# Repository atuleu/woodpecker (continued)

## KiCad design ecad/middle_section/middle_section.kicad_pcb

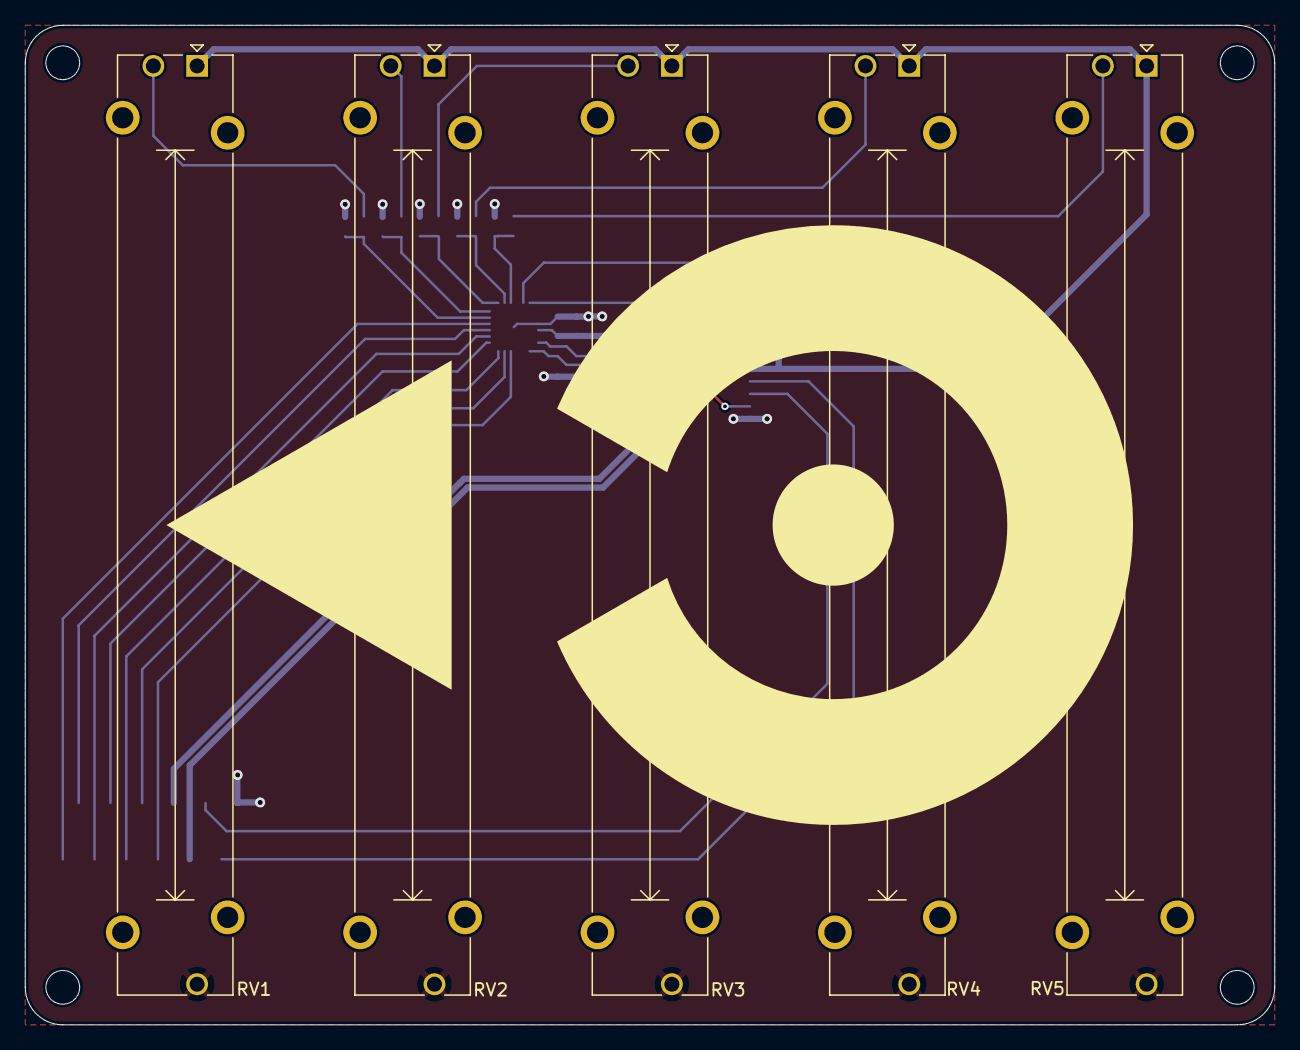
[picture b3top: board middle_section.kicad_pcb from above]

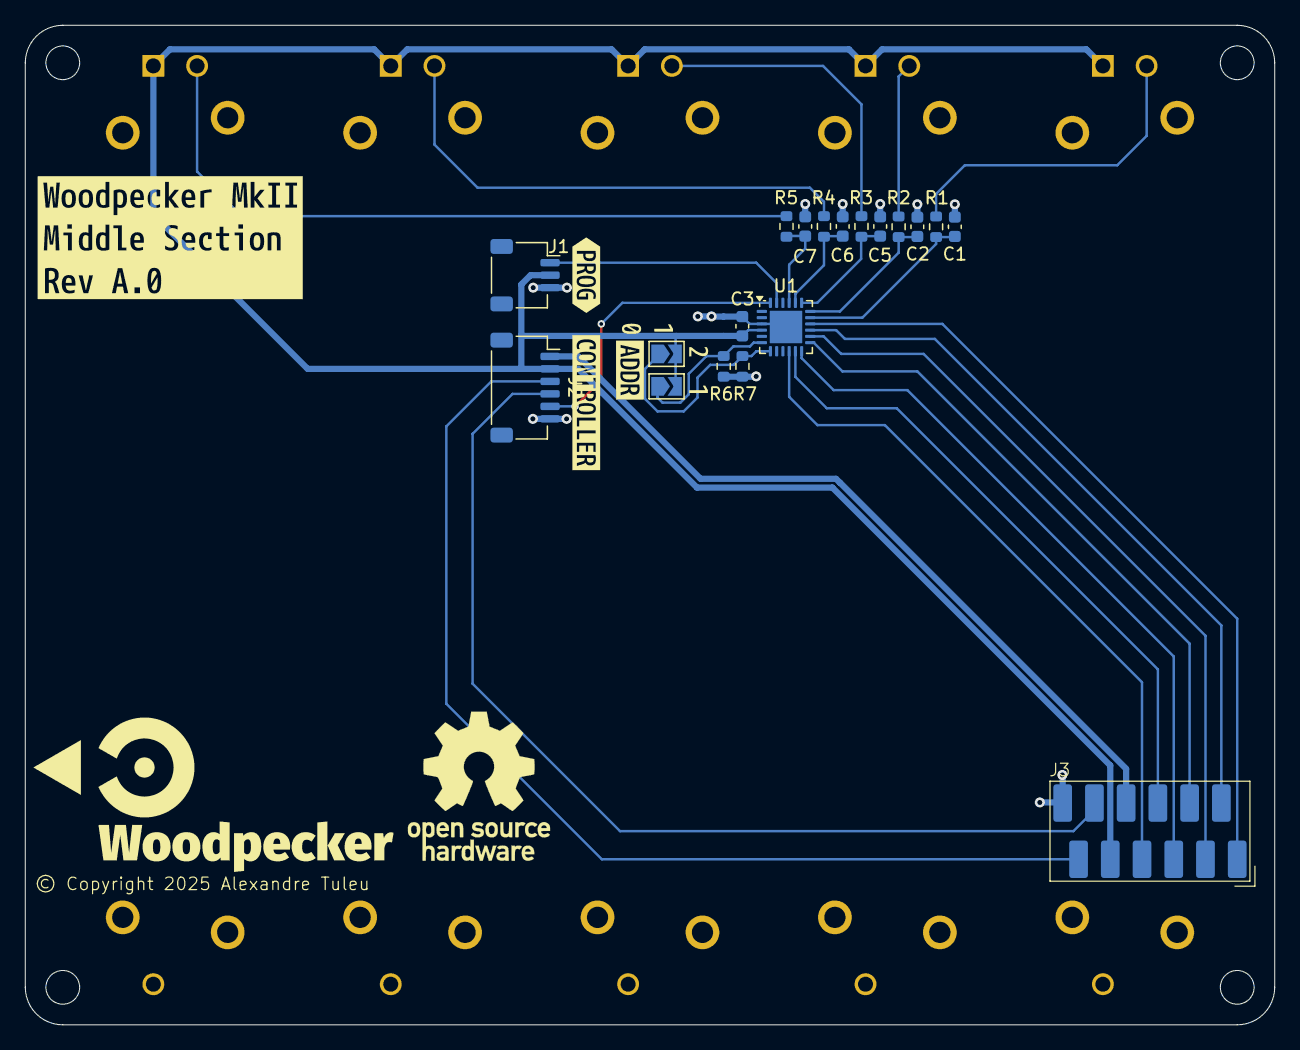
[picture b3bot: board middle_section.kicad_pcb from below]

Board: 2 copper layers, 100.0 x 80.0 mm, 30 parts (25 on the bottom side), 26 nets.

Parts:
C1, C2, C5, C6, C7: 10n; C_0603_1608Metric
C3: 100n; C_0603_1608Metric
J1: JST SH; JST_SH_SM03B-SRSS-TB_1x03-1MP_P1.00mm_Horizontal
J2: JST SH 6P; JST_SH_SM06B-SRSS-TB_1x06-1MP_P1.00mm_Horizontal
J3: Micro-MaTch 2x06; TE_Micro-MaTch_1-188275-2_2x06_P1.27mm_Vertical
JP1, JP2: SolderJumper_2_Open; SolderJumper-2_P1.3mm_Open_TrianglePad1.0x1.5mm
R1, R2, R3, R4, R5: 100; R_0603_1608Metric
R6, R7: 33k; R_0603_1608Metric
RV1, RV2, RV3, RV4, RV5: PTA6043; Potentiometer_Bourns_PTA6043_Single_Slide
U1: ATtiny1617-M; QFN-24-1EP_4x4mm_P0.5mm_EP2.6x2.6mm
kibuzzard-68CC21B9: G***; kibuzzard-68CC21B9
kibuzzard-68CC21E1: G***; kibuzzard-68CC21E1
kibuzzard-68CC21F8: G***; kibuzzard-68CC21F8
kibuzzard-68CC26E5: G***; kibuzzard-68CC26E5
kibuzzard-68CC214D: G***; kibuzzard-68CC214D
kibuzzard-68CC259B: G***; kibuzzard-68CC259B

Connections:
+3V3: C3.1, J1.2, J2.2, J3.9, JP1.2 (B), JP2.2 (B), RV1.1, RV2.1, RV3.1, RV4.1, RV5.1, U1.4 (VCC)
+5V: J2.1, J3.8
/A0: JP1.1 (A), R6.1, U1.6 (PA5)
/A1: JP2.1 (A), R7.1, U1.7 (PA6)
/CH0: C1.1, R1.2, U1.17 (PC0)
/CH0_RAW: R1.1, RV1.2
/CH1: C2.1, R2.2, U1.18 (PC1)
/CH1_RAW: R2.1, RV2.2
/CH2: C5.1, R3.2, U1.19 (PC2)
/CH2_RAW: R3.1, RV3.2
/CH3: C6.1, R4.2, U1.20 (PC3)
/CH3_RAW: R4.1, RV4.2
/CH4: C7.1, R5.2, U1.21 (PC4)
/CH4_RAW: R5.1, RV5.2
/COL1: J3.1, U1.16 (PB0)
/COL2: J3.2, U1.15 (PB1)
/COL3: J3.3, U1.14 (PB2)
/COL4: J3.4, U1.13 (PB3)
/COL5: J3.5, U1.12 (PB4)
/R5_SW: J3.7, U1.10 (PB6)
/R6_SW: J3.6, U1.11 (PB5)
/SCL: J2.4, J3.10
/SDA: J2.3, J3.11
/TX: J2.5, U1.24 (PA1)
/UDPI: J1.1, U1.23 (~RESET/PA0)
GND: C1.2, C2.2, C3.2, C5.2, C6.2, C7.2, J1.3, J2.6, J3.12, R6.2, R7.2, RV1.3, RV2.3, RV3.3, RV4.3, RV5.3, U1.3 (GND), U1.25 (GND)

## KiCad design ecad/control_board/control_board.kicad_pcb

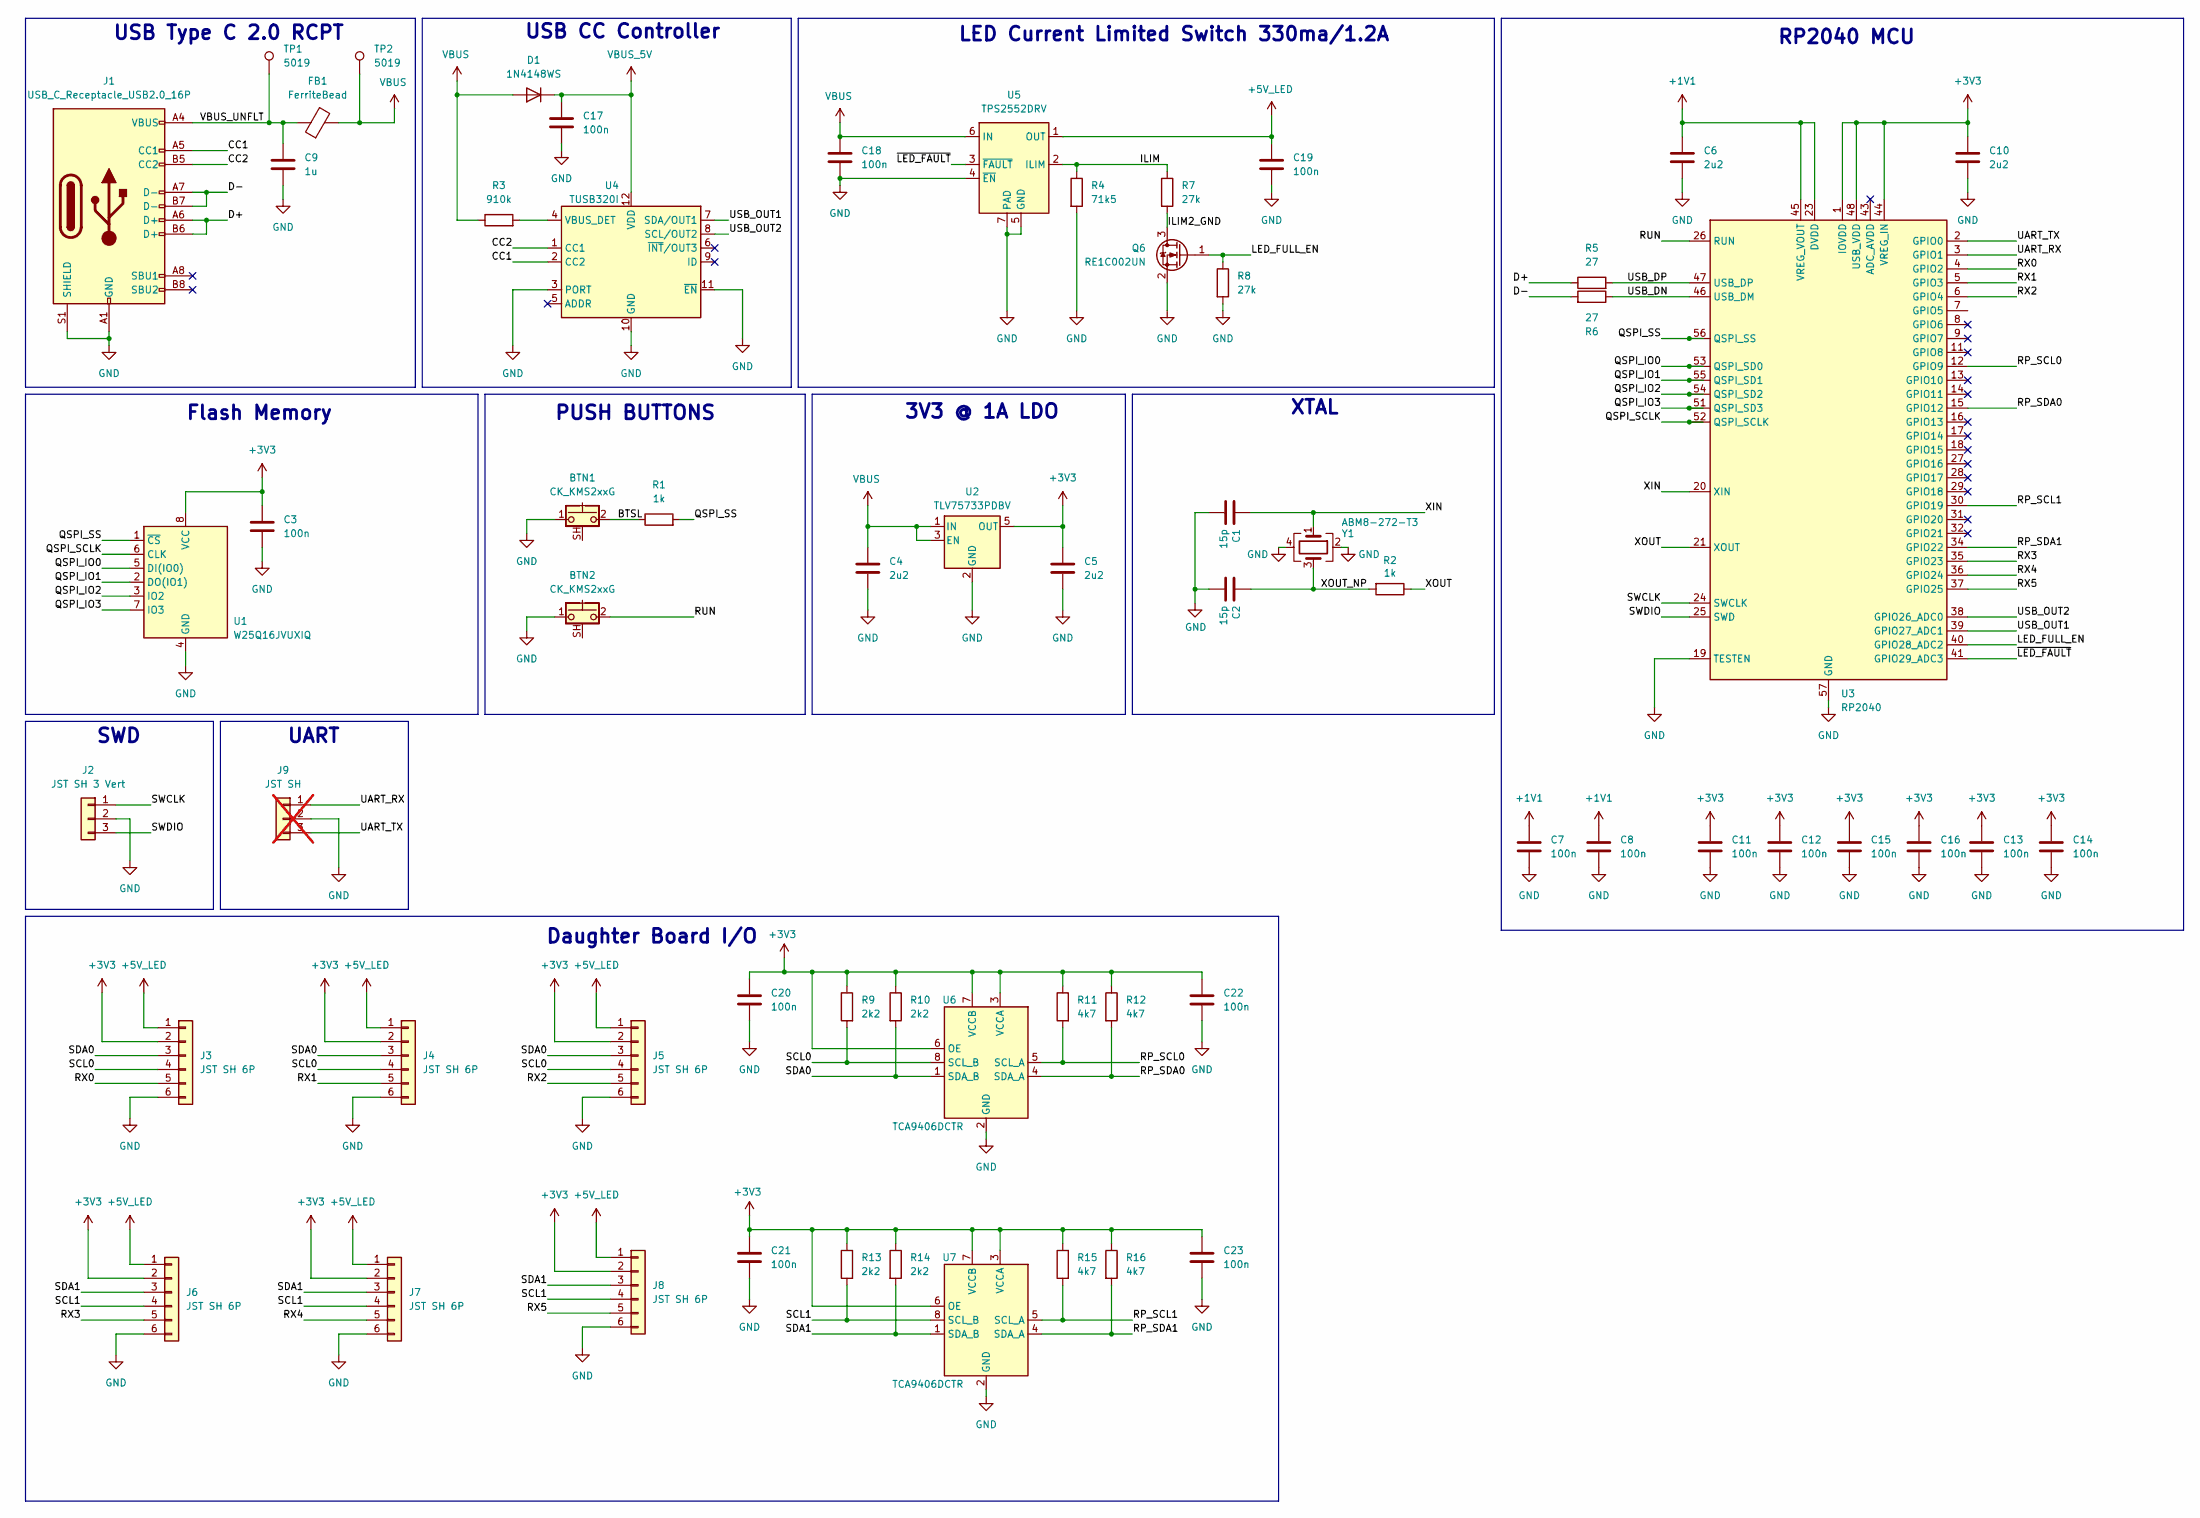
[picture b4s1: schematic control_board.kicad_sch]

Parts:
BTN1, BTN2: CK_KMS2xxG; SW_SPST_CK_KMS2xxGP; MPN KMS231GP LFS
C1, C2: 15p; C_0402_1005Metric; MPN GCM1555C1H150JA16D
C3, C7, C8, C11, C12, C13, C14, C15, C16, C17, C18, C19: 100n; C_0402_1005Metric; MPN CL05B104KP5NNNC
C4, C5: 2u2; C_0603_1608Metric; MPN CL10B225KP8NNNC
C6, C10: 2u2; C_0402_1005Metric; MPN GRM155Z71A225KE01D
C9: 1u; C_0603_1608Metric; MPN CL10B105KP8NNNC
C20, C21, C22, C23: 100n; C_0603_1608Metric; MPN CL10B104KB8NNWC
D1: 1N4148WS; D_SOD-323; MPN 1N4148WS
FB1: FerriteBead; R_1206_3216Metric; MPN HCB 3216KF-501T30
J1: USB_C_Receptacle_USB2.0_16P; USB_C_Receptacle_GCT_USB4105-xx-A_16P_TopMnt_Horizontal; MPN USB4105-GF-A
J2: JST SH 3 Vert; JST_SH_SM03B-SRSS-TB_1x03-1MP_P1.00mm_Horizontal; MPN SM03B-SRSS-TB
J3, J4, J5, J6, J7, J8: JST SH 6P; JST_SH_SM06B-SRSS-TB_1x06-1MP_P1.00mm_Horizontal; MPN SM06B-SRSS-TB
J9: JST SH; JST_SH_SM03B-SRSS-TB_1x03-1MP_P1.00mm_Horizontal; MPN BM03B-SRSS-TB; not fitted
Q6: RE1C002UN; SOT-416; MPN RE1C002UN
R1, R2: 1k; R_0402_1005Metric; MPN RC0402FR-071KL
R3: 910k; R_0402_1005Metric; MPN RC0402FR-07910KL
R4: 71k5; R_0402_1005Metric; MPN RC0402FR-1371K5L
R5, R6: 27; R_0402_1005Metric; MPN RC0402FR-0727RL
R7, R8: 27k; R_0402_1005Metric; MPN RC0402FR-0727KL
R9, R10, R13, R14: 2k2; R_0603_1608Metric; MPN RC0603FR-072K2L
R11, R12, R15, R16: 4k7; R_0603_1608Metric; MPN RC0603FR-074K7L
TP1, TP2: 5019; TestPoint_Keystone_5019_Miniature; MPN 5019
U1: W25Q16JVUXIQ; Winbond_USON-8-1EP_3x2mm_P0.5mm_EP0.2x1.6mm; MPN W25Q16JVUXIQ TR
U2: TLV75733PDBV; SOT-23-5; MPN TLV75733PDBV
U3: RP2040; QFN-56-1EP_7x7mm_P0.4mm_EP3.2x3.2mm; MPN RP2040
U4: TUSB320I; Texas_X2QFN-12_1.6x1.6mm_P0.4mm; MPN TUSB320LI
U5: TPS2552DRV; Texas_WSON-6-1EP_2x2mm_P0.65mm_EP1x1.6mm_ThermalVias; MPN TPS2552DRVR
U6, U7: TCA9406DCTR; SSOP-8_2.95x2.8mm_P0.65mm; MPN TCA9406DCTR
Y1: ABM8-272-T3; Crystal_SMD_3225-4Pin_3.2x2.5mm; MPN ABM8-272-T3

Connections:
+1V1: C6.1, C7.1, C8.1, U3.23 (DVDD), U3.45 (VREG_VOUT), U3.50 (DVDD)
+3V3: C3.1, C5.1, C10.1, C11.1, C12.1, C13.1, C14.1, C15.1, C16.1, C20.1, C21.1, C22.1, C23.1, J3.2, J4.2, J5.2, J6.2, J7.2, J8.2, R9.1, R10.1, R11.1, R12.1, R13.1, R14.1, R15.1, R16.1, U1.8 (VCC), U2.5 (OUT), U3.1 (IOVDD), U3.10 (IOVDD), U3.22 (IOVDD), U3.33 (IOVDD), U3.42 (IOVDD), U3.44 (VREG_IN), U3.48 (USB_VDD), U3.49 (IOVDD), U6.3 (VCCA), U6.6 (OE), U6.7 (VCCB), U7.3 (VCCA), U7.6 (OE), U7.7 (VCCB)
+5V_LED: C19.1, J3.1, J4.1, J5.1, J6.1, J7.1, J8.1, U5.1 (OUT)
/BTSL: BTN1.2, R1.1
/CC1: J1.A5 (CC1), U4.2 (CC2)
/CC2: J1.B5 (CC2), U4.1 (CC1)
/D+: J1.A6 (D+), J1.B6 (D+), R5.1
/D-: J1.A7 (D-), J1.B7 (D-), R6.2
/ILIM: R4.1, R7.1, U5.2 (ILIM)
/ILIM2_GND: Q6.3 (D), R7.2
/LED_FULL_EN: Q6.1 (G), R8.1, U3.40 (GPIO28_ADC2)
/QSPI_IO0: U1.5 (DI(IO0)), U3.53 (QSPI_SD0)
/QSPI_IO1: U1.2 (DO(IO1)), U3.55 (QSPI_SD1)
/QSPI_IO2: U1.3 (IO2), U3.54 (QSPI_SD2)
/QSPI_IO3: U1.7 (IO3), U3.51 (QSPI_SD3)
/QSPI_SCLK: U1.6 (CLK), U3.52 (QSPI_SCLK)
/QSPI_SS: R1.2, U1.1 (~CS), U3.56 (QSPI_SS)
/RP_SCL0: R11.2, U3.12 (GPIO9), U6.5 (SCL_A)
/RP_SCL1: R15.2, U3.30 (GPIO19), U7.5 (SCL_A)
/RP_SDA0: R12.2, U3.15 (GPIO12), U6.4 (SDA_A)
/RP_SDA1: R16.2, U3.34 (GPIO22), U7.4 (SDA_A)
/RUN: BTN2.2, U3.26 (RUN)
/RX0: J3.5, U3.4 (GPIO2)
/RX1: J4.5, U3.5 (GPIO3)
/RX2: J5.5, U3.6 (GPIO4)
/RX3: J6.5, U3.35 (GPIO23)
/RX4: J7.5, U3.36 (GPIO24)
/RX5: J8.5, U3.37 (GPIO25)
/SCL0: J3.4, J4.4, J5.4, R9.2, U6.8 (SCL_B)
/SCL1: J6.4, J7.4, J8.4, R13.2, U7.8 (SCL_B)
/SDA0: J3.3, J4.3, J5.3, R10.2, U6.1 (SDA_B)
/SDA1: J6.3, J7.3, J8.3, R14.2, U7.1 (SDA_B)
/SWCLK: J2.1, U3.24 (SWCLK)
/SWDIO: J2.3, U3.25 (SWD)
/UART_RX: J9.1, U3.3 (GPIO1)
/UART_TX: J9.3, U3.2 (GPIO0)
/USB_DN: R6.1, U3.46 (USB_DM)
/USB_DP: R5.2, U3.47 (USB_DP)
/USB_OUT1: U3.39 (GPIO27_ADC1), U4.7 (SDA/OUT1)
/USB_OUT2: U3.38 (GPIO26_ADC0), U4.8 (SCL/OUT2)
/VBUS_UNFLT: C9.1, FB1.1, J1.A4 (VBUS), J1.A9 (VBUS), J1.B4 (VBUS), J1.B9 (VBUS), TP1.1
/XIN: C1.1, U3.20 (XIN), Y1.1
/XOUT: R2.1, U3.21 (XOUT)
/XOUT_NP: C2.1, R2.2, Y1.3
/~LED_FAULT: U3.41 (GPIO29_ADC3), U5.3 (~FAULT)
GND: BTN1.1, BTN2.1, C1.2, C2.2, C3.2, C4.2, C5.2, C6.2, C7.2, C8.2, C9.2, C10.2, C11.2, C12.2, C13.2, C14.2, C15.2, C16.2, C17.2, C18.2, C19.2, C20.2, C21.2, C22.2, C23.2, J1.A1 (GND), J1.A12 (GND), J1.B1 (GND), J1.B12 (GND), J1.S1 (SHIELD), J2.2, J3.6, J4.6, J5.6, J6.6, J7.6, J8.6, J9.2, Q6.2 (S), R4.2, R8.2, U1.4 (GND), U2.2 (GND), U3.19 (TESTEN), U3.57 (GND), U4.3 (PORT), U4.10 (GND), U4.11 (~EN), U5.4 (~EN), U5.5 (GND), U5.7 (PAD), U6.2 (GND), U7.2 (GND), Y1.2, Y1.4
unnamed: R3.2, U4.4 (VBUS_DET)
VBUS: C4.1, C18.1, D1.2 (A), FB1.2, R3.1, TP2.1, U2.1 (IN), U2.3 (EN), U5.6 (IN)
VBUS_5V: C17.1, D1.1 (K), U4.12 (VDD)

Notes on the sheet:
Daughter Board I/O
USB CC Controller
XTAL
PUSH BUTTONS
LED Current Limited Switch 330ma/1.2A
Flash Memory
UART
SWD
RP2040 MCU
3V3 @ 1A LDO
USB Type C 2.0 RCPT

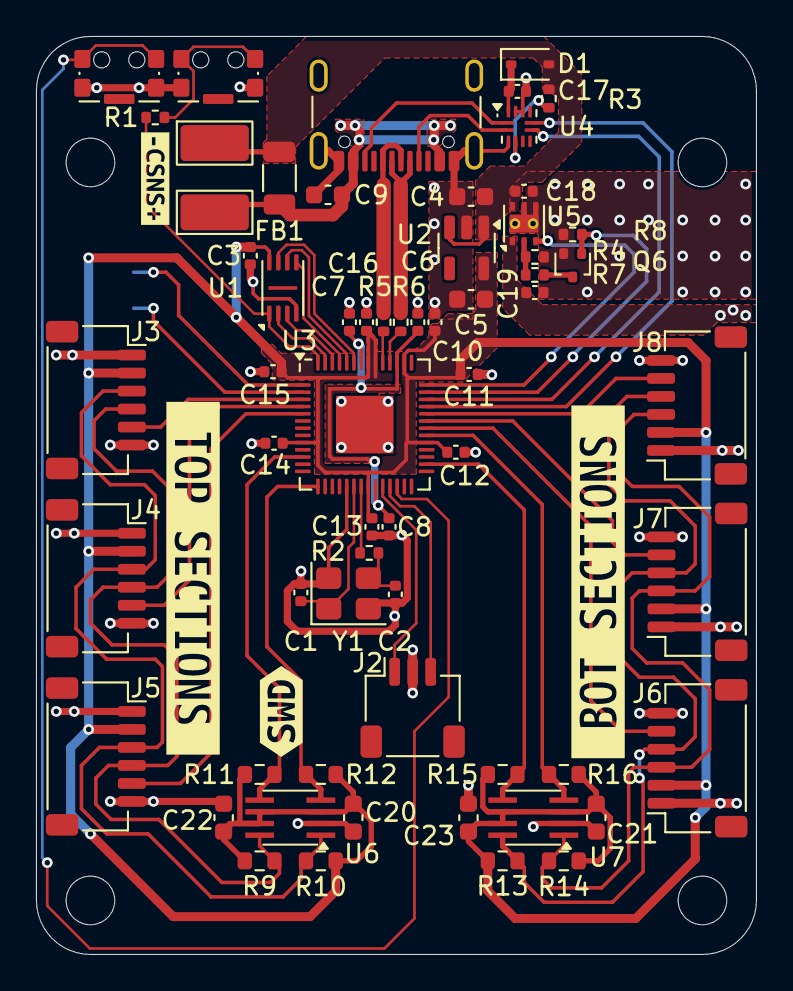
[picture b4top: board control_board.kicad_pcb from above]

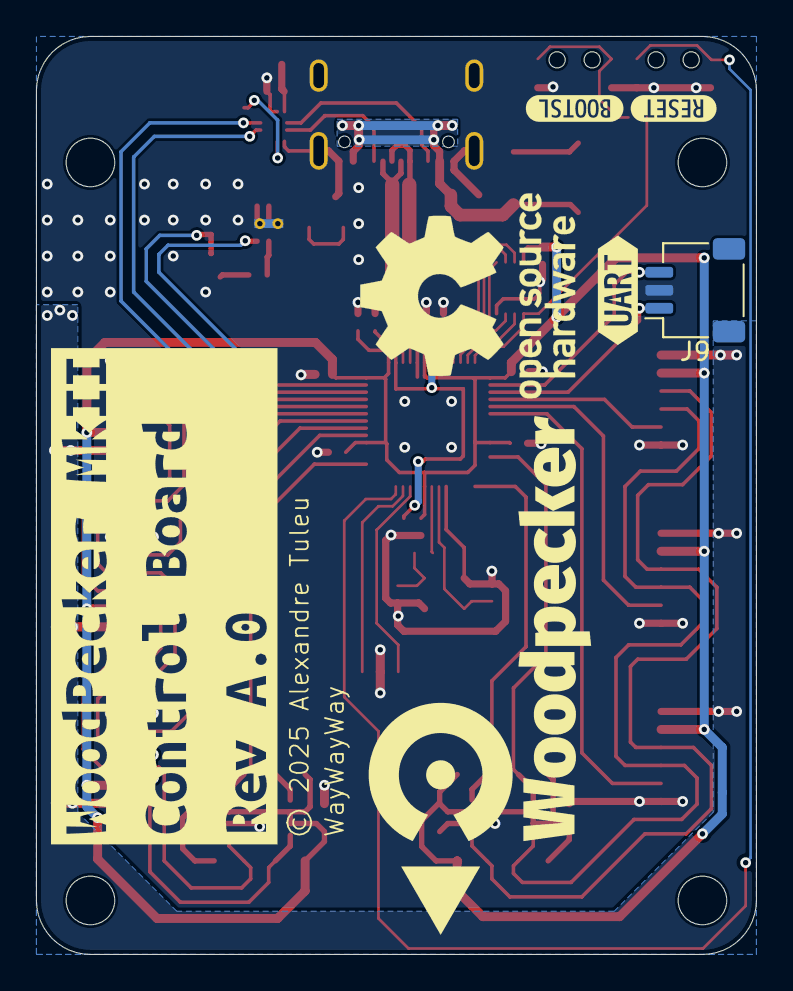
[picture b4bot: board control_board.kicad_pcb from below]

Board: 2 copper layers, 40.0 x 51.0 mm, 71 parts (5 on the bottom side), 49 nets.

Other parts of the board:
kibuzzard-68C95CAF: G***; kibuzzard-68C95CAF
kibuzzard-68C95DDD: G***; kibuzzard-68C95DDD
kibuzzard-68C98DA6: G***; kibuzzard-68C98DA6
kibuzzard-68CC7F6C: G***; kibuzzard-68CC7F6C
kibuzzard-68CC7F87: G***; kibuzzard-68CC7F87
kibuzzard-68CC835E: G***; kibuzzard-68CC835E
kibuzzard-68CC8382: G***; kibuzzard-68CC8382
kibuzzard-68CD18AE: G***; kibuzzard-68CD18AE

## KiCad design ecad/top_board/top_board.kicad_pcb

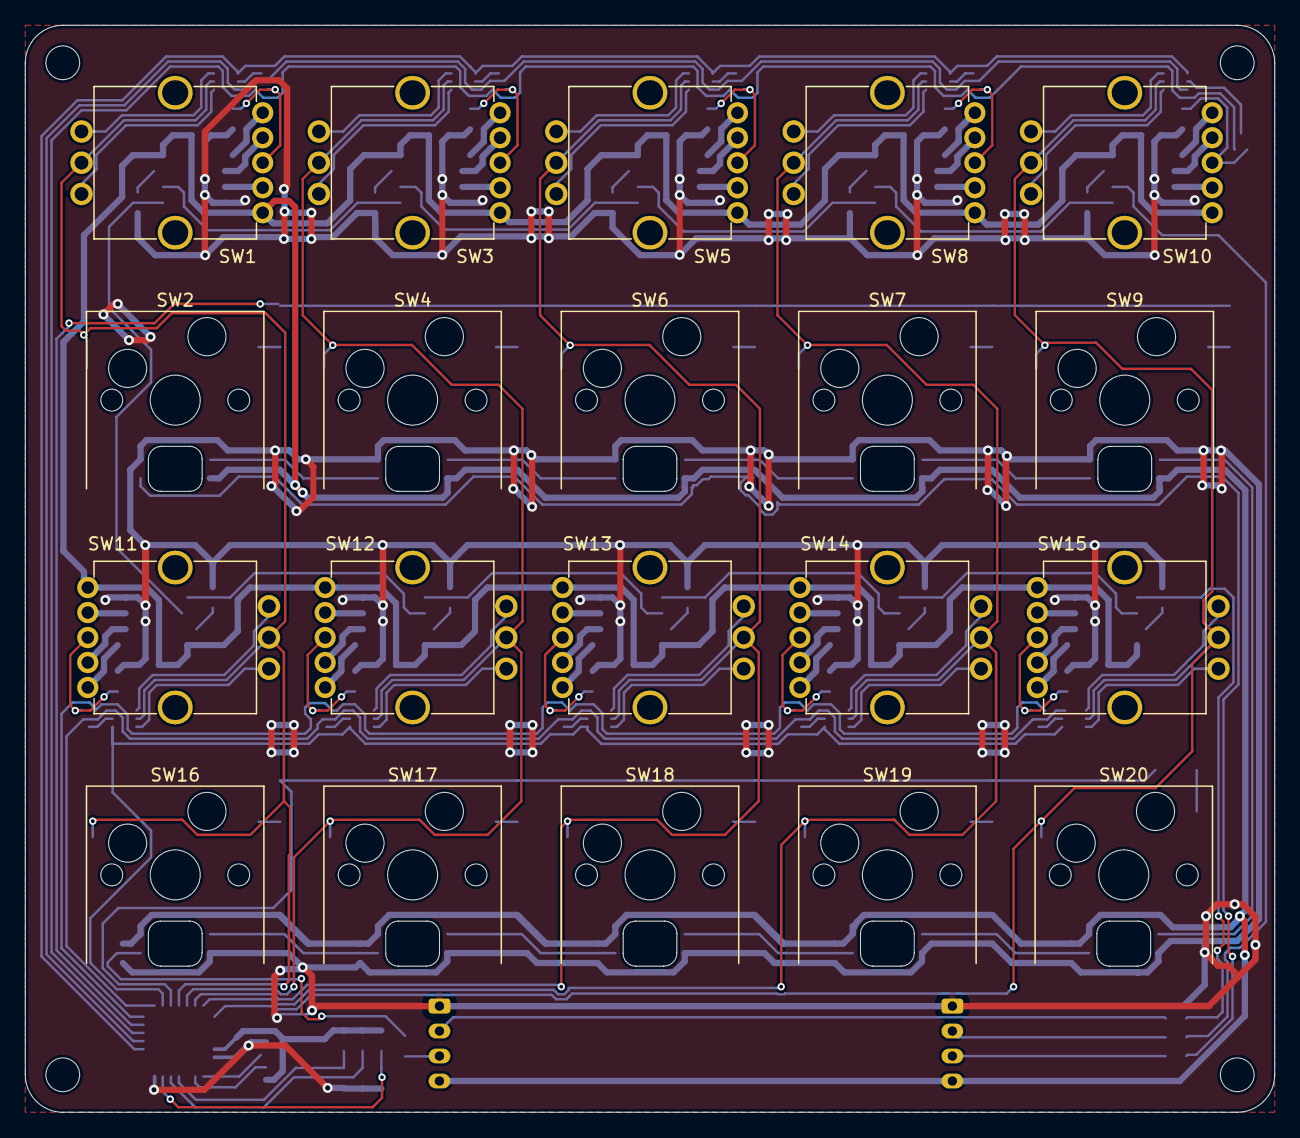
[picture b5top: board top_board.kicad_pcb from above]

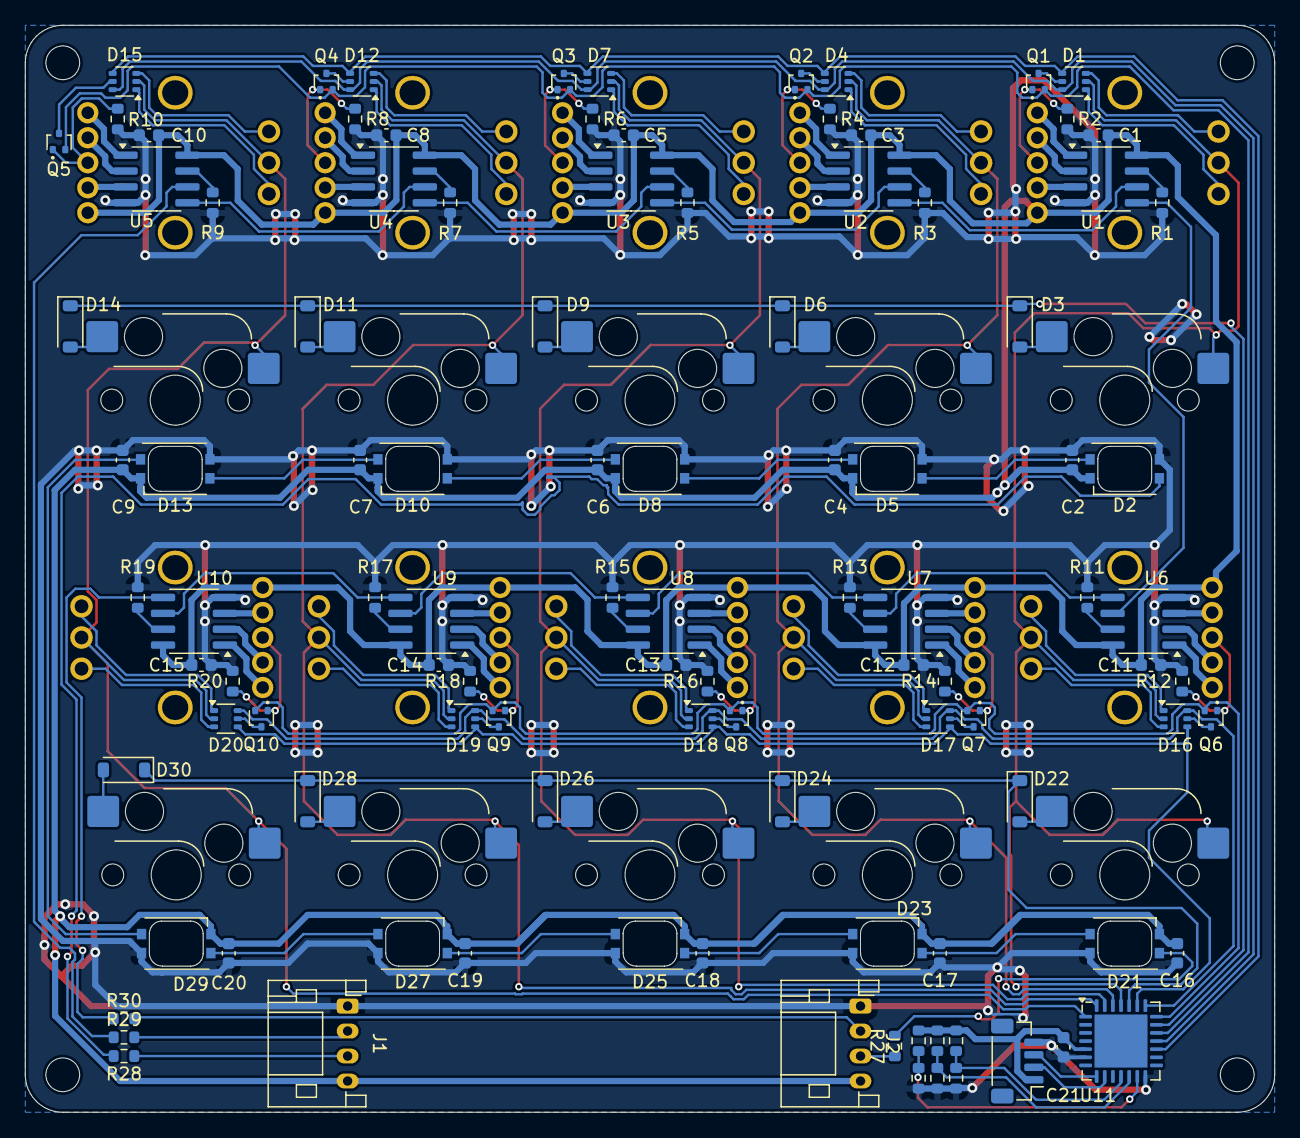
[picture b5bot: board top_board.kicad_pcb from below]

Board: 2 copper layers, 100.0 x 87.0 mm, 125 parts (105 on the bottom side), 137 nets.

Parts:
C1, C2, C3, C4, C5, C6, C7, C8, C9, C10, C11, C12, C13, C14, C15, C16, C17, C18, C19, C20, C21: 100n; C_0603_1608Metric
D1, D4, D7, D12, D15, D16, D17, D18, D19, D20: BAS16TW; SOT-363_SC-70-6
D2, D5, D8, D10, D13, D21, D23, D25, D27, D29: IN-PI32TAR; LED_Inolux_IN-PI32TAR_PLCC4_3.2x2.8mm_P1.5mm
D3, D6, D9, D11, D14, D22, D24, D26, D28, D30: 1N4148W; D_SOD-123
J1, J2: JST PH; JST_PH_S4B-PH-K_1x04_P2.00mm_Horizontal
J3: JST SH; JST_SH_BM04B-SRSS-TB_1x04-1MP_P1.00mm_Vertical
Q1, Q2, Q3, Q4, Q5, Q6, Q7, Q8, Q9, Q10: RE1C002UN; SOT-416
R1, R2, R3, R4, R5, R6, R7, R8, R9, R10, R11, R12, R13, R14, R15, R16, R17, R18, R19, R20, R21, R22, R23, R24, R25, R26: 11k; R_0603_1608Metric
R27, R28, R29, R30: 33; R_0603_1608Metric
SW1, SW3, SW5, SW8, SW10, SW11, SW12, SW13, SW14, SW15: PEL12T; PEL12T-4xxxS-S1024
SW2, SW4, SW6, SW7, SW9, SW16, SW17, SW18, SW19, SW20: SW_Push; SW_Hotswap_Kailh_MX_1.00u
U1, U2, U3, U4, U5, U6, U7, U8, U9, U10: TLC5973; SOIC-8_3.9x4.9mm_P1.27mm
U11: MCP23017_ML; QFN-28-1EP_6x6mm_P0.65mm_EP4.25x4.25mm

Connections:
+3V3: C21.1, J3.1, R21.1, R22.1, R23.1, U11.5 (VDD)
+5V: C1.1, C2.1, C3.1, C4.1, C5.1, C6.1, C7.1, C8.1, C9.1, C10.1, C11.1, C12.1, C13.1, C14.1, C15.1, C16.1, C17.1, C18.1, C19.1, C20.1, D2.1 (VDD), D5.1 (VDD), D8.1 (VDD), D10.1 (VDD), D13.1 (VDD), D21.1 (VDD), D23.1 (VDD), D25.1 (VDD), D27.1 (VDD), D29.1 (VDD), J1.4, J2.4, SW1.5 (A), SW3.5 (A), SW5.5 (A), SW8.5 (A), SW10.5 (A), SW11.5 (A), SW12.5 (A), SW13.5 (A), SW14.5 (A), SW15.5 (A), U1.8 (VCC), U2.8 (VCC), U3.8 (VCC), U4.8 (VCC), U5.8 (VCC), U6.8 (VCC), U7.8 (VCC), U8.8 (VCC), U9.8 (VCC), U10.8 (VCC)
/A0: R22.2, R26.1, U11.11 (A0)
/A1: R21.2, R25.1, U11.12 (A1)
/A2: R23.2, R24.1, U11.13 (A2)
/COL1: D1.2 (A), D16.2 (A), SW1.C, SW2.1, SW11.C, SW16.1, U11.25 (GPB0)
/COL2: D4.2 (A), D17.2 (A), SW3.C, SW4.1, SW12.C, SW17.1, U11.26 (GPB1)
/COL3: D7.2 (A), D18.2 (A), SW5.C, SW6.1, SW13.C, SW18.1, U11.27 (GPB2)
/COL4: D12.2 (A), D19.2 (A), SW7.1, SW8.C, SW14.C, SW19.1, U11.28 (GPB3)
/COL5: D15.2 (A), D20.2 (A), SW9.1, SW10.C, SW15.C, SW20.1, U11.1 (GPB4)
/DIN: J1.3, R28.1
/DOUT: J2.3, R27.1
/KeyboardKey_COL1/DIN: D2.4 (DIN), R28.2
/KeyboardKey_COL1/DOUT: D2.2 (DOUT), D5.4 (DIN)
/KeyboardKey_COL1/SW_ND: D3.2 (A), SW2.2
/KeyboardKey_COL2/DOUT: D5.2 (DOUT), D8.4 (DIN)
/KeyboardKey_COL2/SW_ND: D6.2 (A), SW4.2
/KeyboardKey_COL3/DOUT: D8.2 (DOUT), D10.4 (DIN)
/KeyboardKey_COL3/SW_ND: D9.2 (A), SW6.2
/KeyboardKey_COL4/DOUT: D10.2 (DOUT), D13.4 (DIN)
/KeyboardKey_COL4/SW_ND: D11.2 (A), SW7.2
/KeyboardKey_COL5/SW_ND: D14.2 (A), SW9.2
/KeyboardKey_COL6/DIN: D21.4 (DIN), D23.2 (DOUT)
/KeyboardKey_COL6/DOUT: D21.2 (DOUT), R27.2
/KeyboardKey_COL6/SW_ND: D22.2 (A), SW16.2
/KeyboardKey_COL7/DIN: D23.4 (DIN), D25.2 (DOUT)
/KeyboardKey_COL7/SW_ND: D24.2 (A), SW17.2
/KeyboardKey_COL8/DIN: D25.4 (DIN), D27.2 (DOUT)
/KeyboardKey_COL8/SW_ND: D26.2 (A), SW18.2
/KeyboardKey_COL9/SW_ND: D28.2 (A), SW19.2
/KeyboardKey_COL10/DIN: D13.2 (DOUT), D29.4 (DIN)
/KeyboardKey_COL10/DOUT: D27.4 (DIN), D29.2 (DOUT)
/KeyboardKey_COL10/SW_ND: D30.2 (A), SW20.2
/R1_QA: D1.4 (K), D4.4 (K), D7.4 (K), D12.4 (K), D15.4 (K), U11.17 (GPA0)
/R1_QB: D1.6 (K), D4.6 (K), D7.6 (K), D12.6 (K), D15.6 (K), U11.18 (GPA1)
/R1_SW: Q1.2 (S), Q2.2 (S), Q3.2 (S), Q4.2 (S), Q5.2 (S), U11.19 (GPA2)
/R2_SW: D3.1 (K), D6.1 (K), D9.1 (K), D11.1 (K), D14.1 (K), U11.20 (GPA3)
/R3_QA: D16.4 (K), D17.4 (K), D18.4 (K), D19.4 (K), D20.4 (K), U11.23 (GPA6)
/R3_QB: D16.6 (K), D17.6 (K), D18.6 (K), D19.6 (K), D20.6 (K), U11.22 (GPA5)
/R3_SW: Q6.2 (S), Q7.2 (S), Q8.2 (S), Q9.2 (S), Q10.2 (S), U11.21 (GPA4)
/R4_SW: D22.1 (K), D24.1 (K), D26.1 (K), D28.1 (K), D30.1 (K), U11.24 (GPA7)
/RotaryEncoder_COL1/H_QA: D1.3 (A), SW1.A
/RotaryEncoder_COL1/H_QB: D1.1 (A), SW1.B
/RotaryEncoder_COL1/H_SW: Q1.1 (G), R2.1, SW1.3
/RotaryEncoder_COL1/OUTB: SW1.4 (BK), U1.3 (OUT2)
/RotaryEncoder_COL1/OUTG: SW1.2 (GK), U1.2 (OUT1)
/RotaryEncoder_COL1/OUTR: SW1.1 (RK), U1.1 (OUT0)
/RotaryEncoder_COL1/Q_HS: D1.5 (K), Q1.3 (D)
/RotaryEncoder_COL1/SDI: U1.6 (SDI), U2.5 (SDO)
/RotaryEncoder_COL1/SDO: U1.5 (SDO), U6.6 (SDI)
/RotaryEncoder_COL1/VREF: R1.1, U1.7 (IREF)
/RotaryEncoder_COL2/H_QA: D4.3 (A), SW3.A
/RotaryEncoder_COL2/H_QB: D4.1 (A), SW3.B
/RotaryEncoder_COL2/H_SW: Q2.1 (G), R4.1, SW3.3
/RotaryEncoder_COL2/OUTB: SW3.4 (BK), U2.3 (OUT2)
/RotaryEncoder_COL2/OUTG: SW3.2 (GK), U2.2 (OUT1)
/RotaryEncoder_COL2/OUTR: SW3.1 (RK), U2.1 (OUT0)
/RotaryEncoder_COL2/Q_HS: D4.5 (K), Q2.3 (D)
/RotaryEncoder_COL2/SDI: U2.6 (SDI), U3.5 (SDO)
/RotaryEncoder_COL2/VREF: R3.1, U2.7 (IREF)
/RotaryEncoder_COL3/H_QA: D7.3 (A), SW5.A
/RotaryEncoder_COL3/H_QB: D7.1 (A), SW5.B
/RotaryEncoder_COL3/H_SW: Q3.1 (G), R6.1, SW5.3
/RotaryEncoder_COL3/OUTB: SW5.4 (BK), U3.3 (OUT2)
/RotaryEncoder_COL3/OUTG: SW5.2 (GK), U3.2 (OUT1)
/RotaryEncoder_COL3/OUTR: SW5.1 (RK), U3.1 (OUT0)
/RotaryEncoder_COL3/Q_HS: D7.5 (K), Q3.3 (D)
/RotaryEncoder_COL3/SDI: U3.6 (SDI), U4.5 (SDO)
/RotaryEncoder_COL3/VREF: R5.1, U3.7 (IREF)
/RotaryEncoder_COL4/H_QA: D12.3 (A), SW8.A
/RotaryEncoder_COL4/H_QB: D12.1 (A), SW8.B
/RotaryEncoder_COL4/H_SW: Q4.1 (G), R8.1, SW8.3
/RotaryEncoder_COL4/OUTB: SW8.4 (BK), U4.3 (OUT2)
/RotaryEncoder_COL4/OUTG: SW8.2 (GK), U4.2 (OUT1)
/RotaryEncoder_COL4/OUTR: SW8.1 (RK), U4.1 (OUT0)
/RotaryEncoder_COL4/Q_HS: D12.5 (K), Q4.3 (D)
/RotaryEncoder_COL4/SDI: U4.6 (SDI), U5.5 (SDO)
/RotaryEncoder_COL4/VREF: R7.1, U4.7 (IREF)
/RotaryEncoder_COL5/H_QA: D15.3 (A), SW10.A
/RotaryEncoder_COL5/H_QB: D15.1 (A), SW10.B
/RotaryEncoder_COL5/H_SW: Q5.1 (G), R10.1, SW10.3
/RotaryEncoder_COL5/OUTB: SW10.4 (BK), U5.3 (OUT2)
/RotaryEncoder_COL5/OUTG: SW10.2 (GK), U5.2 (OUT1)
/RotaryEncoder_COL5/OUTR: SW10.1 (RK), U5.1 (OUT0)
/RotaryEncoder_COL5/Q_HS: D15.5 (K), Q5.3 (D)
/RotaryEncoder_COL5/SDI: R29.1, U5.6 (SDI)
/RotaryEncoder_COL5/VREF: R9.1, U5.7 (IREF)
/RotaryEncoder_COL6/H_QA: D16.3 (A), SW11.A
/RotaryEncoder_COL6/H_QB: D16.1 (A), SW11.B
/RotaryEncoder_COL6/H_SW: Q6.1 (G), R12.1, SW11.3
/RotaryEncoder_COL6/OUTB: SW11.4 (BK), U6.3 (OUT2)
/RotaryEncoder_COL6/OUTG: SW11.2 (GK), U6.2 (OUT1)
/RotaryEncoder_COL6/OUTR: SW11.1 (RK), U6.1 (OUT0)
/RotaryEncoder_COL6/Q_HS: D16.5 (K), Q6.3 (D)
/RotaryEncoder_COL6/SDO: U6.5 (SDO), U7.6 (SDI)
/RotaryEncoder_COL6/VREF: R11.1, U6.7 (IREF)
/RotaryEncoder_COL7/H_QA: D17.3 (A), SW12.A
/RotaryEncoder_COL7/H_QB: D17.1 (A), SW12.B
/RotaryEncoder_COL7/H_SW: Q7.1 (G), R14.1, SW12.3
/RotaryEncoder_COL7/OUTB: SW12.4 (BK), U7.3 (OUT2)
/RotaryEncoder_COL7/OUTG: SW12.2 (GK), U7.2 (OUT1)
/RotaryEncoder_COL7/OUTR: SW12.1 (RK), U7.1 (OUT0)
/RotaryEncoder_COL7/Q_HS: D17.5 (K), Q7.3 (D)
/RotaryEncoder_COL7/SDO: U7.5 (SDO), U8.6 (SDI)
/RotaryEncoder_COL7/VREF: R13.1, U7.7 (IREF)
/RotaryEncoder_COL8/H_QA: D18.3 (A), SW13.A
/RotaryEncoder_COL8/H_QB: D18.1 (A), SW13.B
/RotaryEncoder_COL8/H_SW: Q8.1 (G), R16.1, SW13.3
/RotaryEncoder_COL8/OUTB: SW13.4 (BK), U8.3 (OUT2)
/RotaryEncoder_COL8/OUTG: SW13.2 (GK), U8.2 (OUT1)
/RotaryEncoder_COL8/OUTR: SW13.1 (RK), U8.1 (OUT0)
/RotaryEncoder_COL8/Q_HS: D18.5 (K), Q8.3 (D)
/RotaryEncoder_COL8/SDO: U8.5 (SDO), U9.6 (SDI)
/RotaryEncoder_COL8/VREF: R15.1, U8.7 (IREF)
/RotaryEncoder_COL9/H_QA: D19.3 (A), SW14.A
/RotaryEncoder_COL9/H_QB: D19.1 (A), SW14.B
/RotaryEncoder_COL9/H_SW: Q9.1 (G), R18.1, SW14.3
/RotaryEncoder_COL9/OUTB: SW14.4 (BK), U9.3 (OUT2)
/RotaryEncoder_COL9/OUTG: SW14.2 (GK), U9.2 (OUT1)
/RotaryEncoder_COL9/OUTR: SW14.1 (RK), U9.1 (OUT0)
/RotaryEncoder_COL9/Q_HS: D19.5 (K), Q9.3 (D)
/RotaryEncoder_COL9/VREF: R17.1, U9.7 (IREF)
/RotaryEncoder_COL10/H_QA: D20.3 (A), SW15.A
/RotaryEncoder_COL10/H_QB: D20.1 (A), SW15.B
/RotaryEncoder_COL10/H_SW: Q10.1 (G), R20.1, SW15.3
/RotaryEncoder_COL10/OUTB: SW15.4 (BK), U10.3 (OUT2)
/RotaryEncoder_COL10/OUTG: SW15.2 (GK), U10.2 (OUT1)
/RotaryEncoder_COL10/OUTR: SW15.1 (RK), U10.1 (OUT0)
/RotaryEncoder_COL10/Q_HS: D20.5 (K), Q10.3 (D)
/RotaryEncoder_COL10/SDI: U9.5 (SDO), U10.6 (SDI)
/RotaryEncoder_COL10/SDO: R30.1, U10.5 (SDO)
/RotaryEncoder_COL10/VREF: R19.1, U10.7 (IREF)
/SCK: J3.3, U11.8 (SCK)
/SDA: J3.2, U11.9 (SDA)
/SDIN: J1.2, R29.2
/SDOUT: J2.2, R30.2
GND: C1.2, C2.2, C3.2, C4.2, C5.2, C6.2, C7.2, C8.2, C9.2, C10.2, C11.2, C12.2, C13.2, C14.2, C15.2, C16.2, C17.2, C18.2, C19.2, C20.2, C21.2, D2.3 (GND), D5.3 (GND), D8.3 (GND), D10.3 (GND), D13.3 (GND), D21.3 (GND), D23.3 (GND), D25.3 (GND), D27.3 (GND), D29.3 (GND), J1.1, J2.1, J3.4, R1.2, R2.2, R3.2, R4.2, R5.2, R6.2, R7.2, R8.2, R9.2, R10.2, R11.2, R12.2, R13.2, R14.2, R15.2, R16.2, R17.2, R18.2, R19.2, R20.2, R24.2, R25.2, R26.2, U1.4 (GND), U2.4 (GND), U3.4 (GND), U4.4 (GND), U5.4 (GND), U6.4 (GND), U7.4 (GND), U8.4 (GND), U9.4 (GND), U10.4 (GND), U11.6 (VSS), U11.14 (~RESET)
